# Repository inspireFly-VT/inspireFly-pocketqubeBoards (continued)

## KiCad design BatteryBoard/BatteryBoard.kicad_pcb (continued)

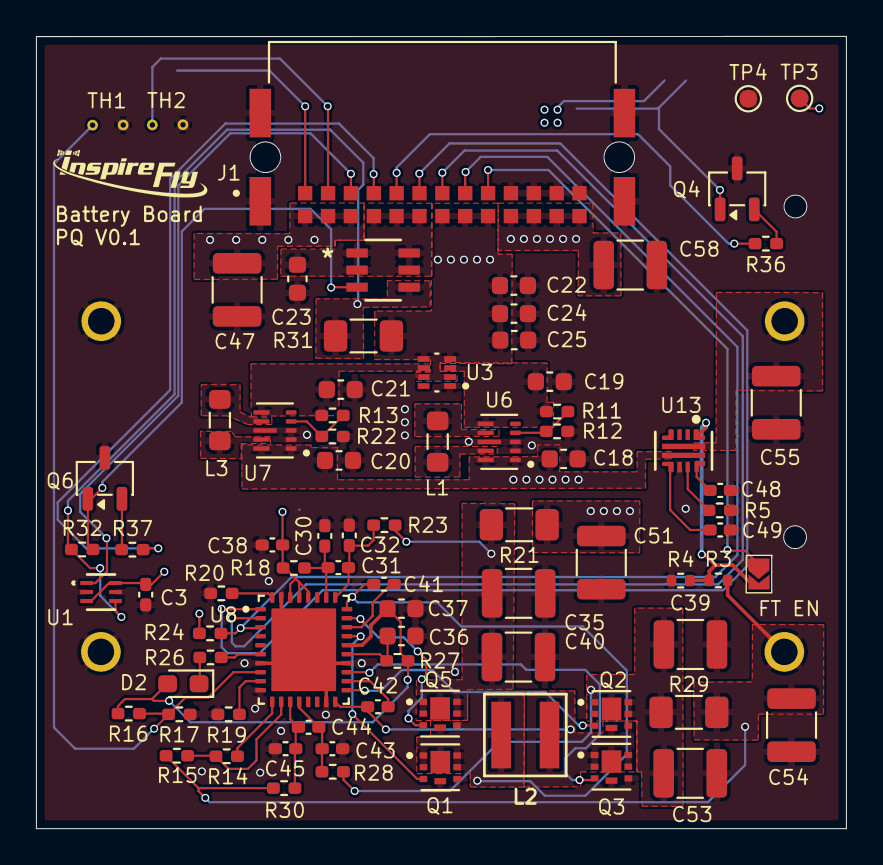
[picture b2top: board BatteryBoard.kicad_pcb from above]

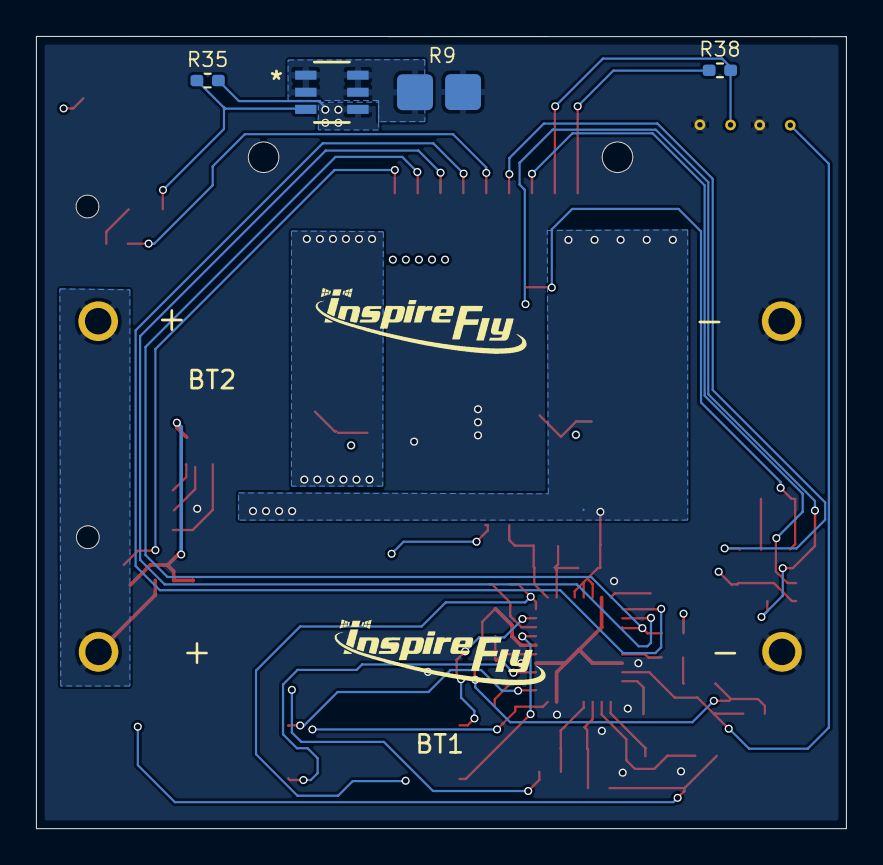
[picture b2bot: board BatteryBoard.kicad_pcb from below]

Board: 4 copper layers, 45.0 x 44.0 mm, 86 parts (6 on the bottom side), 56 nets.

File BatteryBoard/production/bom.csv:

Designator,Footprint,Quantity,Value,LCSC Part #
"BT1, BT2",BAT_BH123A,2,BH123A,
"C18, C19, C20, C21, C22, C23, C24, C25",0603,8,10uF,
"C3, C30, C32, C41, C42, C43, C45",0402,7,100nF,
"C31, C44",0402,2,470nF,
"C35, C39, C40, C47, C51, C53, C54, C55, C58",1210,9,22uF,
"C36, C37",0603,2,4.7uF,
C38,0402,1,1uF,
"C48, C49",0402,2,10nF,
D2,0603,1,LTST-S270KRKT,
J1,HARWIN_M55-7102642R,1,M55-7102642R,
JP1,SmallJumper,1,FTSW EN,
"L1, L3",0805,2,470nH,
L2,IND_SRP4020FA-2R2M_BRN,1,2.2uH,
"Q1, Q2, Q3, Q5",TRANS_PMPB11EN_115,4,"PMPB13XNE,115",
"Q4, Q6",SOT-23-3,2,"T2N7002AK,LM",
"R11, R13",0402,2,280k,
"R12, R19, R22",0402,3,50k,
R14,0402,1,82.5k,
R15,0402,1,143k,
R16,0402,1,6.2k,
R17,0402,1,36k,
"R18, R23, R27, R28, R30",0402,5,10,
R20,0402,1,40k,
"R21, R29, R31",1206,3,5m,
"R24, R26, R32, R35, R38",0402,5,10k,
R3,0402,1,649k,
"R36, R37",0402,2,100,
R4,0402,1,348k,
R5,0402,1,750,
R9,HeaterConnection,1,Heater,
"TH1, TH2",NRBG104F3435B2F,2,NRBG104F3435B2F,
TP3,TestPoint_Pad_D1.0mm,1,3.3V,
TP4,TestPoint_Pad_D1.0mm,1,GND,
U1,SOT_INA185_TEX,1,INA185A4IDRLR,
"U10, U2",SOT_V-T1-GE3_VIS-M,2,SI3477DV-T1-GE3,
U13,RPW0010A-MFG,1,TPS259472ARPWR,
U3,SOTFL50P160X60-8N,1,TPS2117DRLR,
"U6, U7",VREG_TPS63802DLAR,2,TPS63802DLAR,
U8,IC_BQ25756ERRVR,1,BQ25756ERRVR,

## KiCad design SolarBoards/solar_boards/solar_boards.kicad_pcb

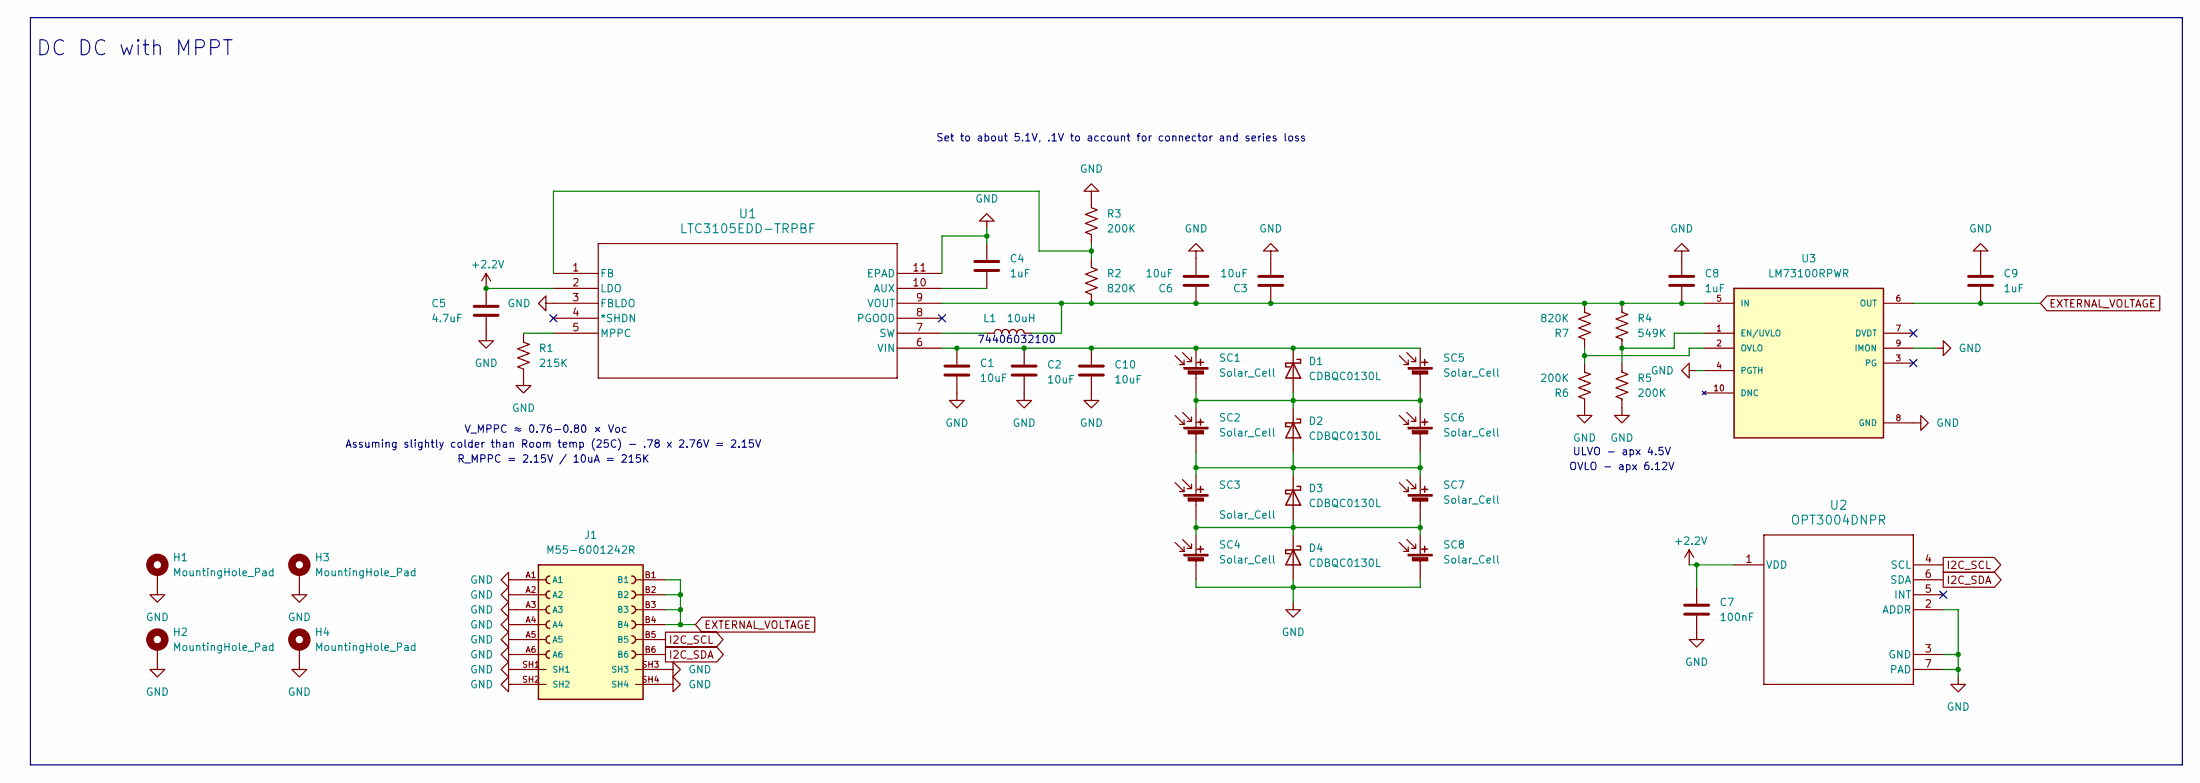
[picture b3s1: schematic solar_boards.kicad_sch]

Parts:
C1, C2, C3, C6, C10: 10uF; C_0603_1608Metric
C4, C8, C9: 1uF; C_0402_1005Metric_Pad0.74x0.62mm_HandSolder
C5: 4.7uF; C_0402_1005Metric_Pad0.74x0.62mm_HandSolder
C7: 100nF; C_0402_1005Metric_Pad0.74x0.62mm_HandSolder
D1, D2, D3, D4: CDBQC0130L; DIODFN100X60X55-2N
H1, H2, H3, H4: MountingHole_Pad; MountingHole_2mm_custom
J1: M55-6001242R; HARWIN_M55-6001242R; PARTREV 8; DigiKey_Part_Number 952-3835-1-ND
L1: 10uH; WE-LQFS_3818
R1: 215K; R_0402_1005Metric_Pad0.72x0.64mm_HandSolder
R2, R7: 820K; R_0402_1005Metric_Pad0.72x0.64mm_HandSolder
R3, R5, R6: 200K; R_0402_1005Metric_Pad0.72x0.64mm_HandSolder
R4: 549K; R_0402_1005Metric_Pad0.72x0.64mm_HandSolder
SC1, SC2, SC3, SC4, SC5, SC6, SC7, SC8: Solar_Cell; SOLAR_KXOB25-14X1F-TR
U1: LTC3105EDD-TRPBF; DFN-10_DD_LIT
U2: OPT3004DNPR; DNP0006A
U3: LM73100RPWR; IC_LM73100RPWR; PARTREV 08/2019

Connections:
+2.2V: C5.1, C7.1, U1.2 (LDO), U2.1 (VDD)
EXTERNAL_VOLTAGE: C9.1, J1.B1, J1.B2, J1.B3, J1.B4, U3.6 (OUT)
GND: C1.2, C2.2, C3.2, C4.1, C5.2, C6.2, C7.2, C8.2, C9.2, C10.2, D4.2 (A), H1.1 (1_1), H2.1 (1_1), H3.1 (1_1), H4.1 (1_1), J1.A1, J1.A2, J1.A3, J1.A4, J1.A5, J1.A6, J1.SH1, J1.SH2, J1.SH3, J1.SH4, R1.2, R3.1, R5.2, R6.1, SC4.2 (-), SC8.2 (-), U1.3 (FBLDO), U1.11 (EPAD), U2.2 (ADDR), U2.3 (GND), U2.7 (PAD), U3.4 (PGTH), U3.8 (GND), U3.9 (IMON)
I2C_SCL: J1.B5, U2.4 (SCL)
I2C_SDA: J1.B6, U2.6 (SDA)
unnamed: D1.2 (A), D2.1 (K), SC1.2 (-), SC2.1 (+), SC5.2 (-), SC6.1 (+)
unnamed: C1.1, C2.1, C10.1, D1.1 (K), SC1.1 (+), SC5.1 (+), U1.6 (VIN)
unnamed: D2.2 (A), D3.1 (K), SC2.2 (-), SC3.1 (+), SC6.2 (-), SC7.1 (+)
unnamed: D3.2 (A), D4.1 (K), SC3.2 (-), SC4.1 (+), SC7.2 (-), SC8.1 (+)
unnamed: C4.2, U1.10 (AUX)
unnamed: R2.1, R3.2, U1.1 (FB)
unnamed: R1.1, U1.5 (MPPC)
unnamed: L1.1, U1.7 (SW)
unnamed: C3.1, C6.1, C8.1, L1.2, R2.2, R4.1, R7.2, U1.9 (VOUT), U3.5 (IN)
unnamed: R4.2, R5.1, U3.1 (EN/UVLO)
unnamed: R6.2, R7.1, U3.2 (OVLO)

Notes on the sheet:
R_MPPC = 2.15V / 10uA = 215K
Assuming slightly colder than Room temp (25C) - .78 x 2.76V = 2.15V
ULVO - apx 4.5V
OVLO - apx 6.12V
74406032100
DC DC with MPPT
Set to about 5.1V, .1V to account for connector and series loss
V_MPPC ≈ 0.76-0.80 × Voc

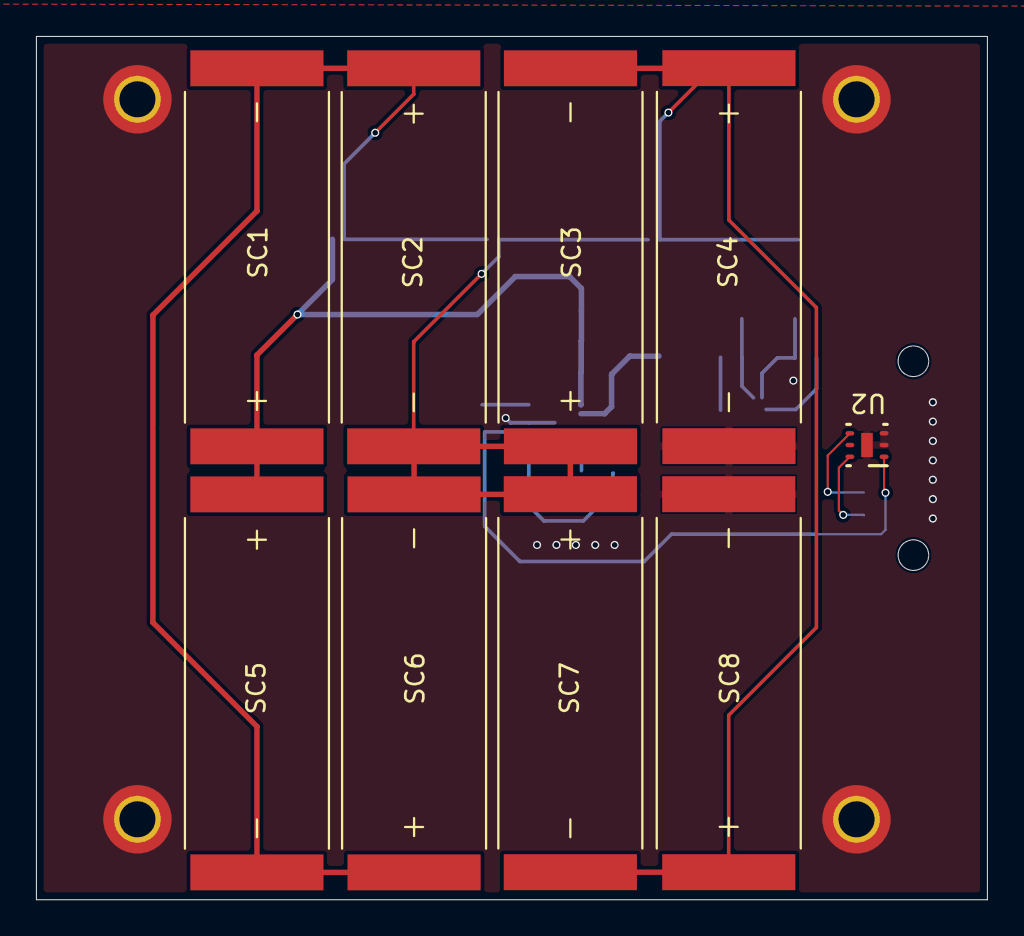
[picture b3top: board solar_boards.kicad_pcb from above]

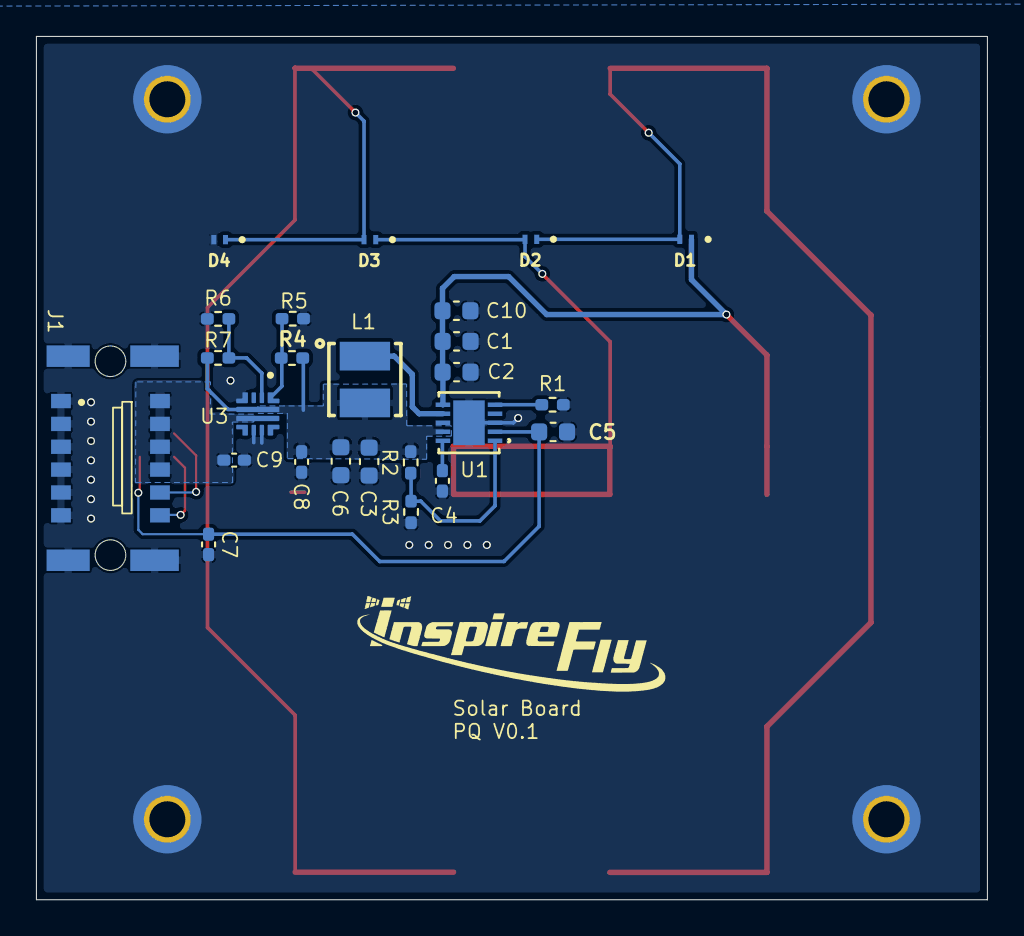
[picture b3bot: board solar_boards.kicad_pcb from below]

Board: 2 copper layers, 52.8 x 48.0 mm, 38 parts (25 on the bottom side), 16 nets.

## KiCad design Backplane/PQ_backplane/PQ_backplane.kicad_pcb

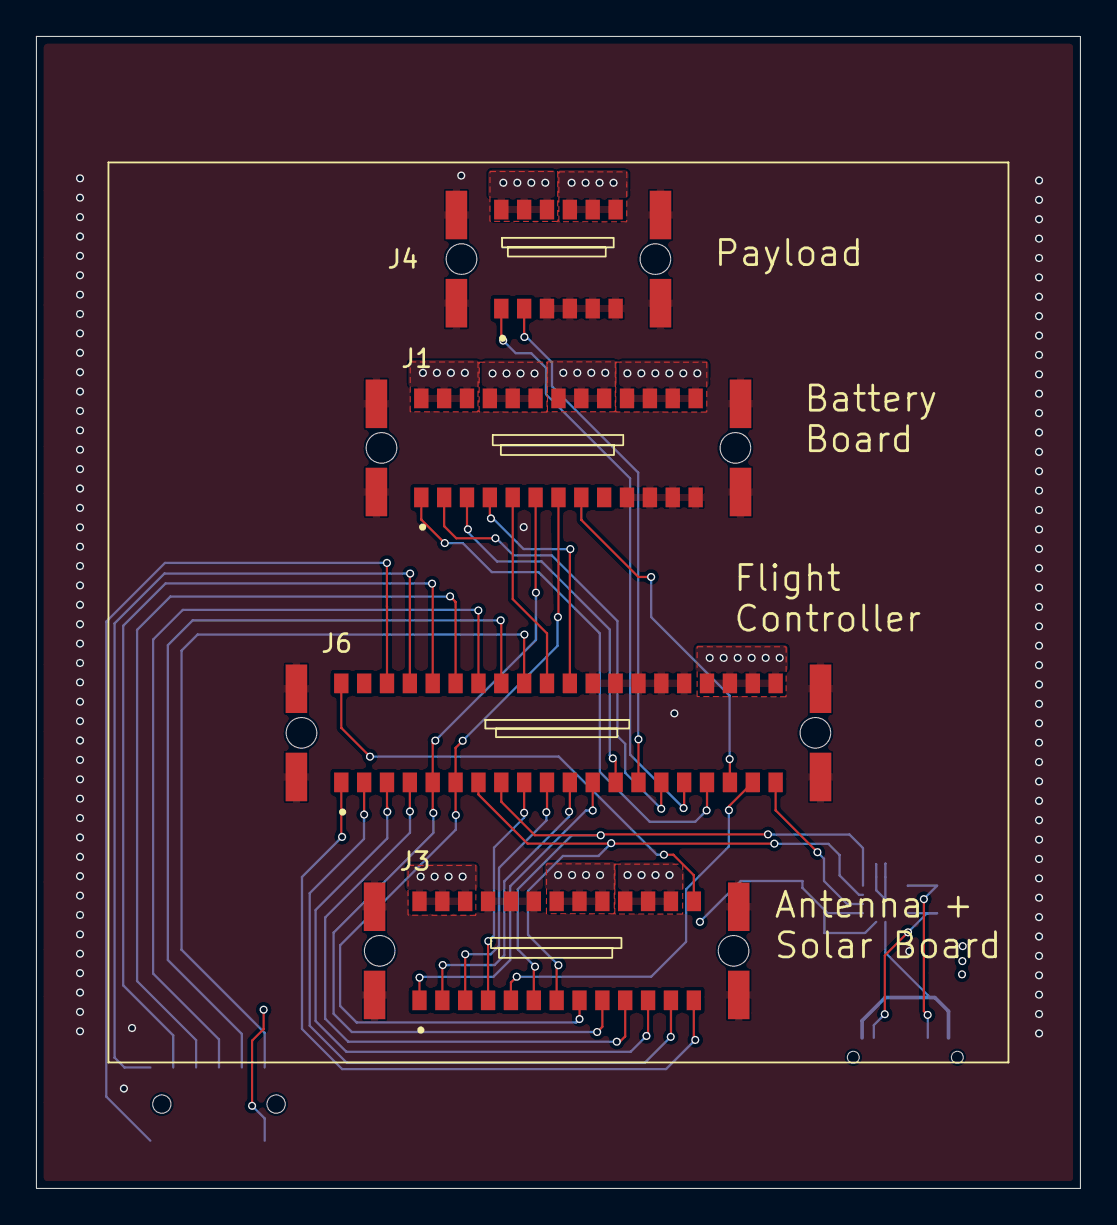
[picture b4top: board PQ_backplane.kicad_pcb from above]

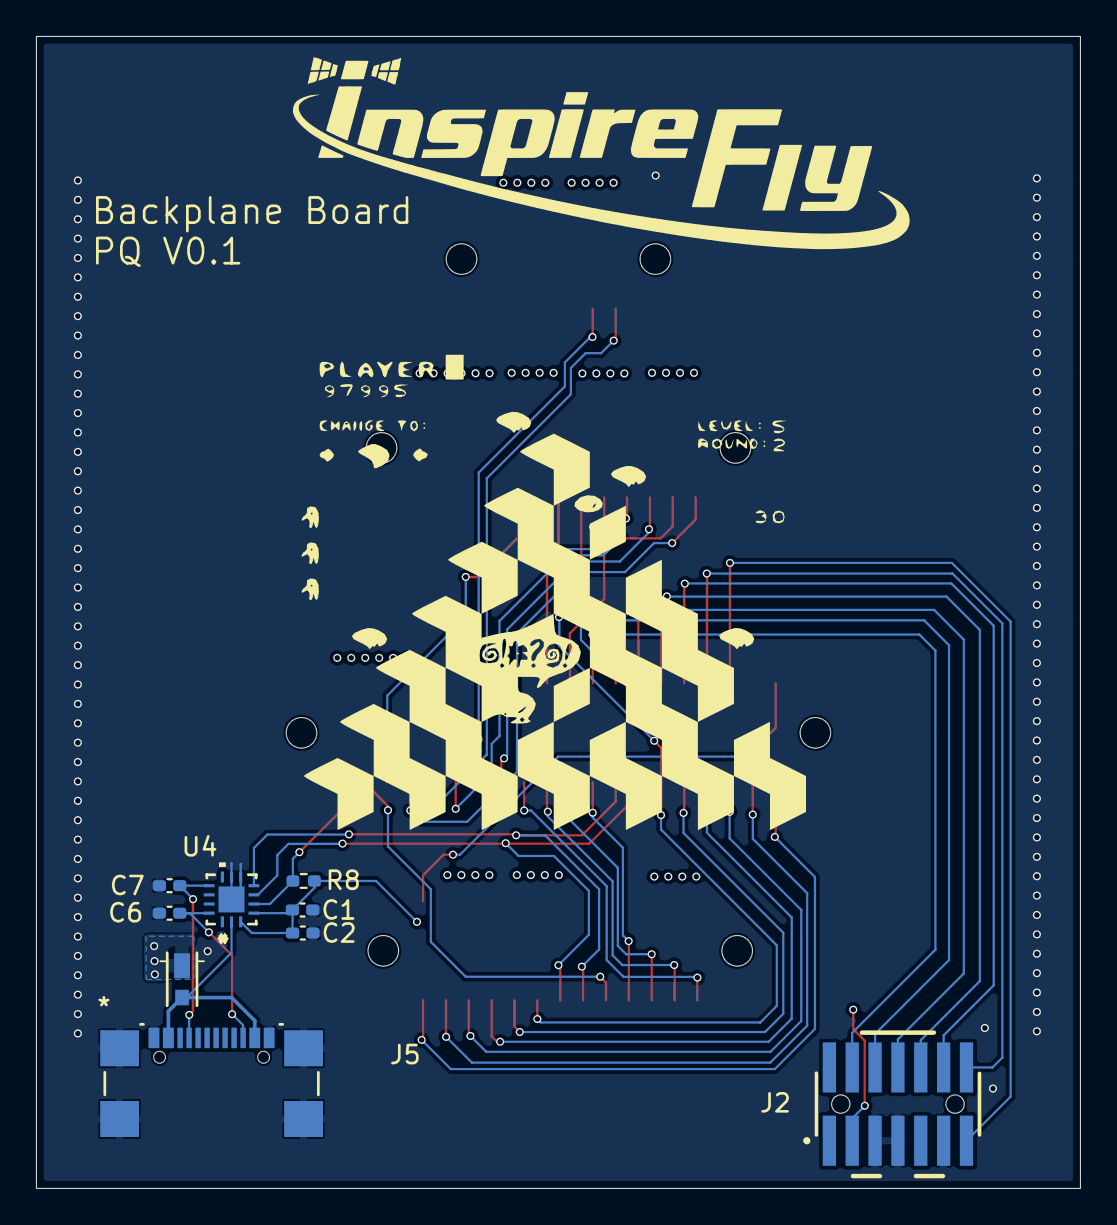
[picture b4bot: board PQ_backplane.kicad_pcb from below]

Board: 4 copper layers, 58.0 x 64.0 mm, 13 parts (9 on the bottom side), 38 nets.

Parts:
C1: 1uF; C_0402_1005Metric_Pad0.74x0.62mm_HandSolder
C2: 100nF; C_0402_1005Metric_Pad0.74x0.62mm_HandSolder
C6, C7: 470pF; C_0402_1005Metric_Pad0.74x0.62mm_HandSolder
D1: MSS2P2-M3/89A; DIODE_MSP3V3
J1, J3: M55-6002642R; HARWIN_M55-6002642R
J2: FTSH-107-01-L-DV-K-A; SAMTEC_FTSH-107-01-L-DV-K-A
J4: M55-6001242R; HARWIN_M55-6001242R
J5: USB4110-GF-A; USB4110-GF-A_GCT
J6: M55-6004042R; HARWIN_M55-6004042R
R8: 2.2k; R_0402_1005Metric_Pad0.72x0.64mm_HandSolder
U4: FUSB302BMPX; MLP14_2P5X2P5_ONS

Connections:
+3.3V: C1.1, C2.1, J1.B7, J1.B8, J1.B9, J2.03, J3.B1, J3.B2, J3.B3, J6.B17, J6.B18, J6.B19, J6.B20, R8.2, U4.3 (VDD), U4.4 (VDD)
ADC1_A1: J1.A3, J6.A13
ADC1_A2: J1.A2, J6.A15
ANT_SPI2_MISO: J3.A2, J6.A11
ANT_SPI2_MOSI: J3.A1, J6.A12
ANT_SPI2_NSS: J3.A3, J6.A10
ANT_SPI2_SCK: J3.A4, J6.A9
BATMANG_INT_DIN: J1.A8, J6.A18
BAT_HEAT_EN: J1.A5, J6.B10
BURN_WIRE_EN: J3.A5, J6.A19
CAN_H: J4.A1, J6.A16
CAN_L: J4.A2, J6.A14
DEBUG_LPUART_RX: J2.14, J6.B4
DEBUG_LPUART_TX: J2.13, J6.B3
EN_THERMISTOR_READ: J1.A1, J6.A17
EXTERNAL_VOLTAGE: D1.1 (K), J1.B1, J1.B2, J1.B3, J3.B10, J3.B11, J3.B12, J4.B4, J4.B5, J4.B6
GND: C1.2, C2.2, C6.2, C7.2, J1.A10, J1.A11, J1.A12, J1.A13, J1.SH1 (Shield), J1.SH2 (Shield), J1.SH3 (Shield), J1.SH4 (Shield), J2.05, J2.07, J2.11, J3.B4, J3.B5, J3.B6, J3.SH1 (Shield), J3.SH2 (Shield), J3.SH3 (Shield), J3.SH4 (Shield), J4.A3, J4.A4, J4.A5, J4.A6, J4.SH1 (Shield), J4.SH2 (Shield), J4.SH3 (Shield), J4.SH4 (Shield), J5.15 (Shield), J5.16 (Shield), J5.17 (Shield), J5.18 (Shield), J5.A1-B12 (GND), J5.A12-B1 (GND), J6.B12, J6.B13, J6.B14, J6.B15, J6.B16, J6.SH1 (Shield), J6.SH2 (Shield), J6.SH3 (Shield), J6.SH4 (Shield), U4.8 (GND), U4.9 (GND), U4.15 (EPAD)
I2C1_SCL: J3.A7, J6.A7, U4.6 (SCL)
I2C1_SDA: J3.A6, J6.A8, U4.7 (SDA)
I2C2_SCL: J1.A6, J3.A9, J6.A5
I2C2_SDA: J1.A7, J3.A8, J6.A6
I2C3_SCL: J3.A11, J6.A3
I2C3_SDA: J3.A10, J6.A4
I2C4_SCL: J3.A13, J6.A1
I2C4_SDA: J3.A12, J6.A2
JTCK/SWCLK: J2.06, J6.B8
JTDI: J2.10, J6.B6
JTMS/SWDIO: J2.04, J6.B9
NRST: J2.12, J6.B5
unnamed: D1.2 (A), J5.A4-B9 (VBUS), J5.A9-B4 (VBUS), U4.2 (VBUS)
unnamed: C7.1, J5.A5 (CC1), U4.11 (CC1)
unnamed: C6.1, J5.B5 (CC2), U4.14 (CC2)
PAYLOAD_3.3V: J1.B4, J1.B5, J1.B6, J4.B1, J4.B2, J4.B3
PAYLOAD_3.3V_EN: J1.A4, J6.B11
PROTECTED_VOLTAGE: J1.B10, J1.B11, J1.B12, J1.B13, J3.B7, J3.B8, J3.B9
RFM_RESET: J3.B13, J6.B1
SWO: J2.08, J6.B7
USBC_PD_INT_N: J6.A20, R8.1, U4.5 (INT_N)

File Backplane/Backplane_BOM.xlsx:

Distributor | Part Number | Part Description | Quantity Per Board
Digikey | CL05B104KA5NNNC | CAP CER 0.1UF 25V X7R 0402 | 1
Digikey | GRM155Z71A105KE01D | CAP CER 1UF 10V X7R 0402 | 1
Digikey | 885012005017 | CAP CER 470PF 10V C0G/NP0 0402 | 2
Digikey | ERA-2VEB2201X | RES 2.2K OHM 0.1% 1/10W 0402 | 1
Digikey | MSS2P2-M3/89A | DIODE SCHOTTKY 20V 2A DO219AD | 1
Digikey | FUSB302BMPX | IC USB TYPE C CTLR PROGR 14-MLP | 1
Digikey | M55-6002642R | CONN RCPT 26POS 0.05 GOLD SMD | 2
Digikey | FTSH-107-01-F-DV-K-P-TR | CONN HEADER SMD 14POS 1.27MM | 1
Digikey | M55-6001242R | CONN RCPT 12POS 0.05 GOLD SMD | 1
Digikey | USB4110-GF-A | CONN RCP USB2.0 TYP C 24P SMD RA | 1
Digikey | M55-6004042R | CONN RCPT 40POS 0.05 GOLD SMD | 1

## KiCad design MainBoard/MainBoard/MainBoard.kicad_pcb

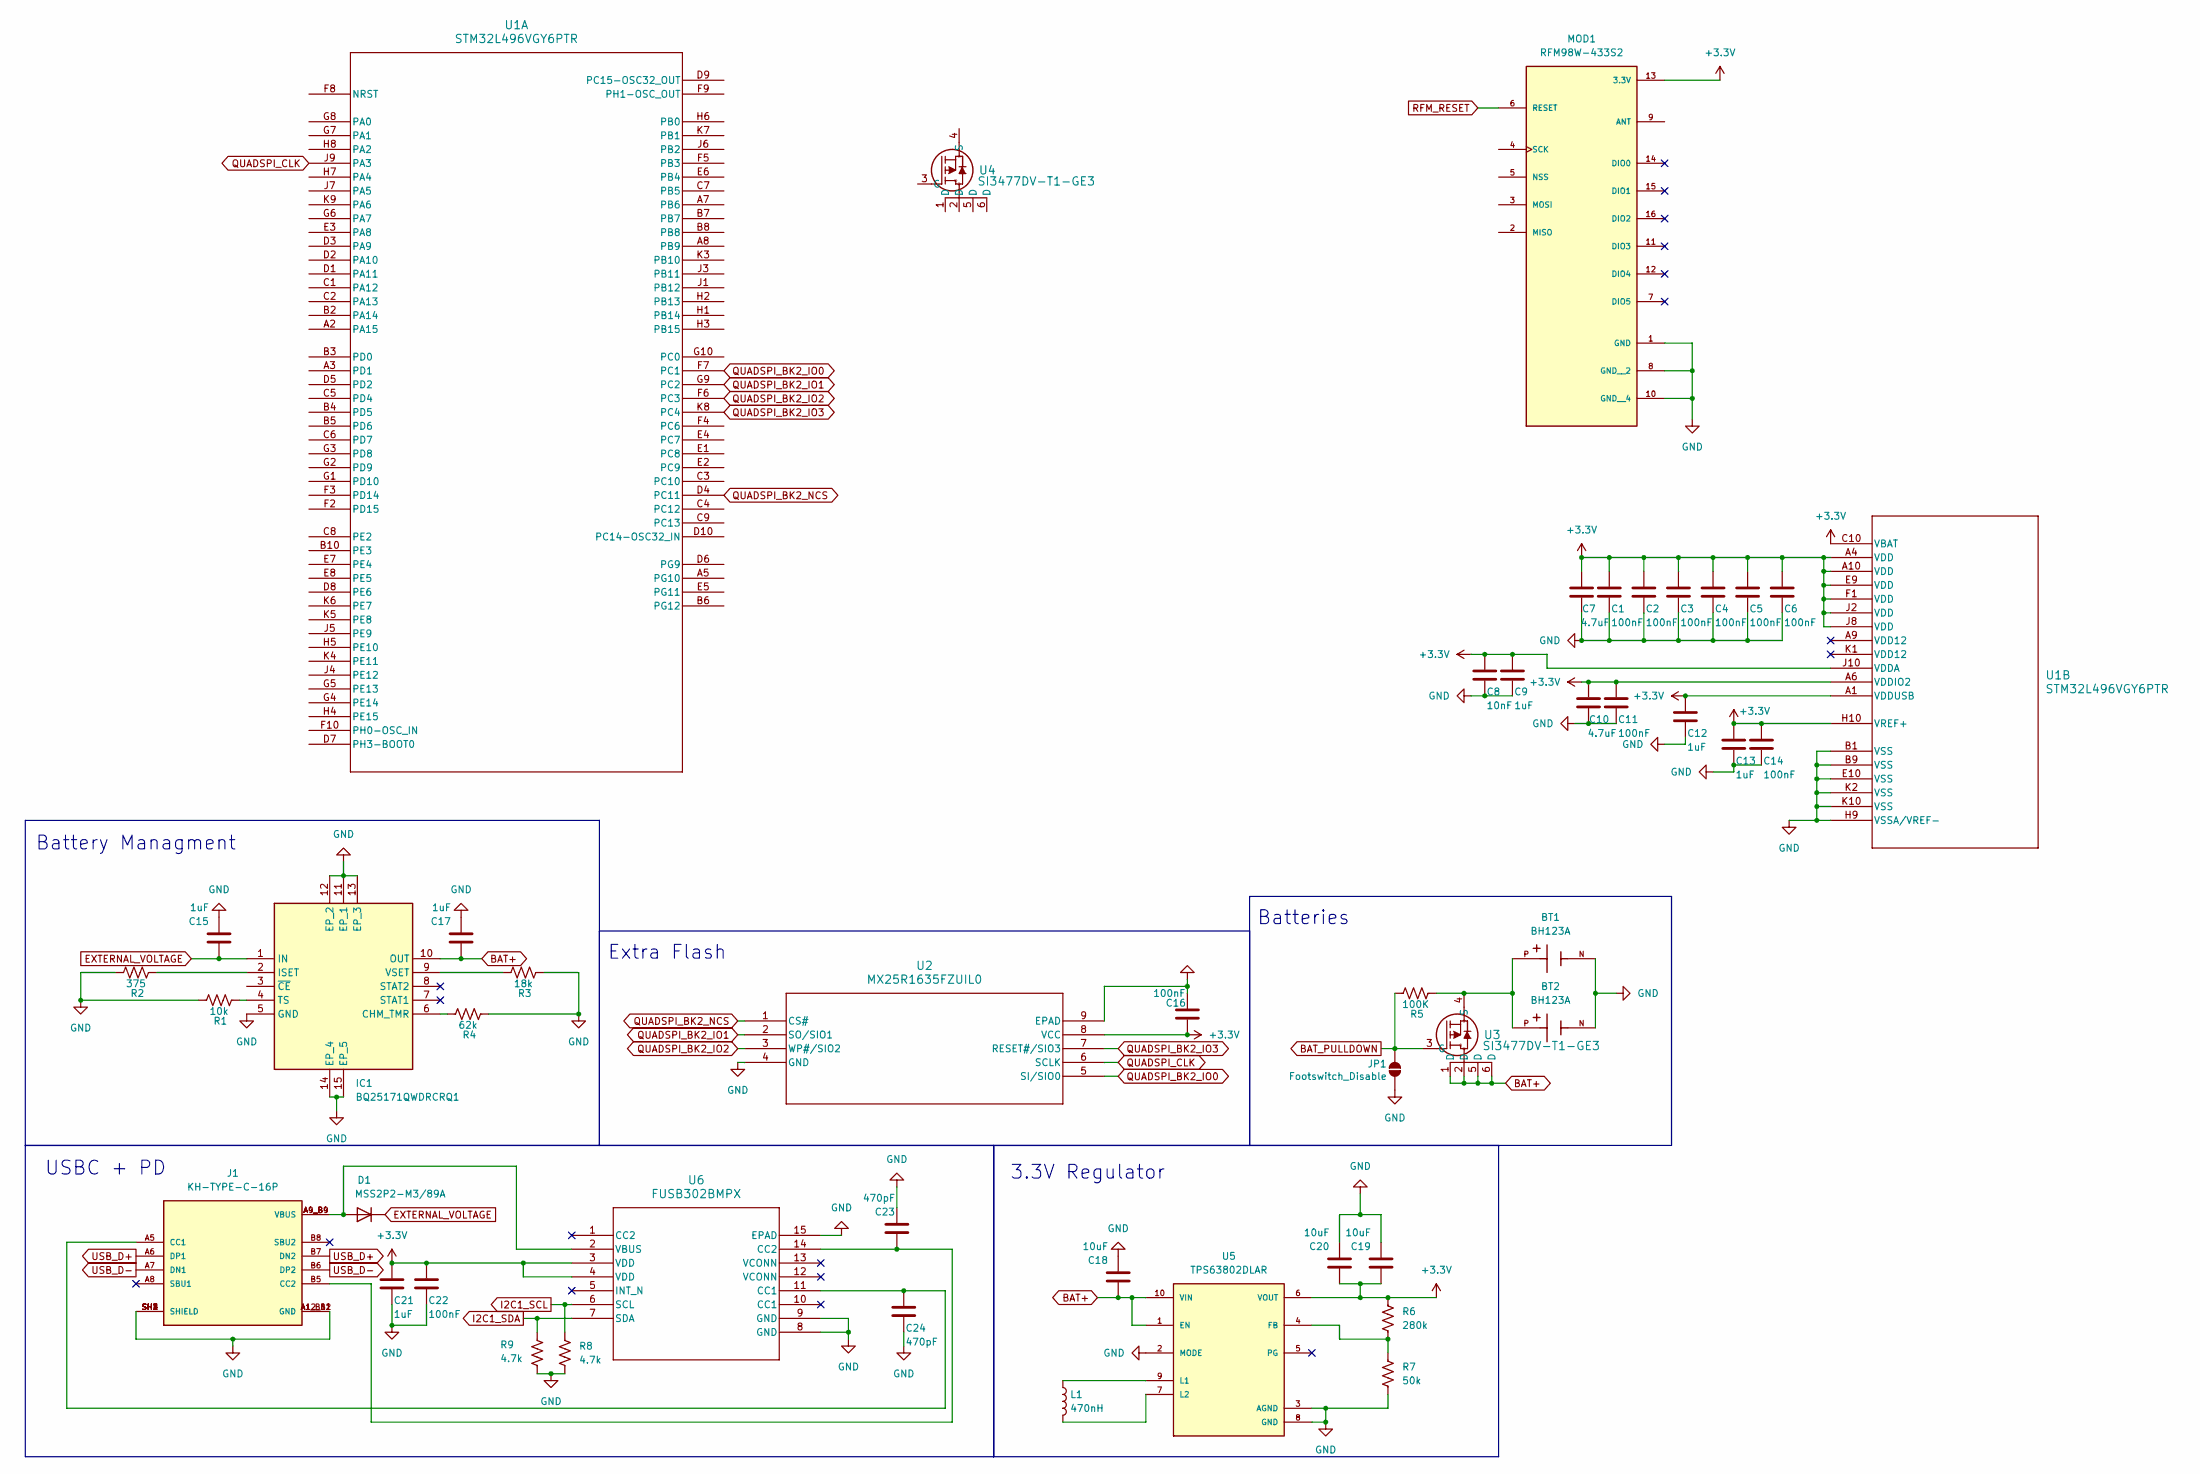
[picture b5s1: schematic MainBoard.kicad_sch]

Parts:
BT1, BT2: BH123A; BAT_BH123A; PARTREV E
C1, C2, C3, C4, C5, C6, C11, C14, C16, C22: 100nF; C_0402_1005Metric_Pad0.74x0.62mm_HandSolder
C7, C10: 4.7uF; C_0402_1005Metric_Pad0.74x0.62mm_HandSolder
C8: 10nF; C_0402_1005Metric_Pad0.74x0.62mm_HandSolder
C9, C12, C13, C15, C17, C21: 1uF; C_0402_1005Metric_Pad0.74x0.62mm_HandSolder
C18, C19, C20: 10uF; C_0402_1005Metric_Pad0.74x0.62mm_HandSolder
C23, C24: 470pF; C_0402_1005Metric_Pad0.74x0.62mm_HandSolder
D1: MSS2P2-M3/89A; DIODE_MSP3V3
IC1: BQ25171QWDRCRQ1; Mouser Part Number 595-BQ25171QWDRCRQ1
J1: KH-TYPE-C-16P; KINGHELM_KH-TYPE-C-16P; PARTREV A0
JP1: Footswitch_Disable; SolderJumper-2_P1.3mm_Open_TrianglePad1.0x1.5mm
L1: 470nH; L_0805_2012Metric_Pad1.15x1.40mm_HandSolder
MOD1: RFM98W-433S2; XCVR_RFM98W-433S2; PARTREV N/A
R1: 10k; R_0402_1005Metric_Pad0.72x0.64mm_HandSolder
R2: 375; R_0402_1005Metric_Pad0.72x0.64mm_HandSolder
R3: 18k; R_0402_1005Metric_Pad0.72x0.64mm_HandSolder
R4: 62k; R_0402_1005Metric_Pad0.72x0.64mm_HandSolder
R5: 100K; R_0402_1005Metric_Pad0.72x0.64mm_HandSolder
R6: 280k; R_0402_1005Metric_Pad0.72x0.64mm_HandSolder
R7: 50k; R_0402_1005Metric_Pad0.72x0.64mm_HandSolder
R8, R9: 4.7k; R_0402_1005Metric_Pad0.72x0.64mm_HandSolder
U1: STM32L496VGY6PTR; STM32L496VGY6TR
U2: MX25R1635FZUIL0; USON-8L-2X3X0P6_MAC
U3, U4: SI3477DV-T1-GE3; SOT_V-T1-GE3_VIS-M
U5: TPS63802DLAR; VREG_TPS63802DLAR; PARTREV B
U6: FUSB302BMPX; MLP14_2P5X2P5_ONS

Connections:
+3.3V: C1.1, C2.1, C3.1, C4.1, C5.1, C6.1, C7.1, C8.1, C9.1, C10.1, C11.1, C12.1, C13.1, C14.1, C16.2, C19.1, C20.1, C21.1, C22.1, MOD1.13 (3.3V), R6.1, U1.A1 (VDDUSB), U1.A4 (VDD), U1.A6 (VDDIO2), U1.A10 (VDD), U1.C10 (VBAT), U1.E9 (VDD), U1.F1 (VDD), U1.H10 (VREF+), U1.J2 (VDD), U1.J8 (VDD), U1.J10 (VDDA), U2.8 (VCC), U5.6 (VOUT), U6.3 (VDD), U6.4 (VDD); also elsewhere on the board
BAT+: C17.1, C18.1, IC1.10 (OUT), U3.1 (D), U3.2 (D), U3.5 (D), U3.6 (D), U5.1 (EN), U5.10 (VIN)
BAT_PULLDOWN: JP1.2 (B), R5.1, U3.3 (G)
EXTERNAL_VOLTAGE: C15.1, D1.1 (K), IC1.1 (IN)
GND: BT1.N, BT2.N, C1.2, C2.2, C3.2, C4.2, C5.2, C6.2, C7.2, C8.2, C9.2, C10.2, C11.2, C12.2, C13.2, C14.2, C15.2, C16.1, C17.2, C18.2, C19.2, C20.2, C21.2, C22.2, C23.2, C24.2, IC1.5 (GND), IC1.11 (EP_1), IC1.12 (EP_2), IC1.13 (EP_3), IC1.14 (EP_4), IC1.15 (EP_5), J1.A1_B12 (GND), J1.A12_B1 (GND), J1.SH1 (SHIELD), J1.SH2 (SHIELD), J1.SH3 (SHIELD), J1.SH4 (SHIELD), JP1.1 (A), MOD1.1 (GND), MOD1.8 (GND__2), MOD1.10 (GND__4), R1.1, R2.1, R3.2, R4.2, R7.2, R8.2, R9.1, U1.B1 (VSS), U1.B9 (VSS), U1.E10 (VSS), U1.H9 (VSSA/VREF-), U1.K2 (VSS), U1.K10 (VSS), U2.4 (GND), U2.9 (EPAD), U5.2 (MODE), U5.3 (AGND), U5.8 (GND), U6.8 (GND), U6.9 (GND), U6.15 (EPAD); also elsewhere on the board
I2C1_SCL: R8.1, U6.6 (SCL)
I2C1_SDA: R9.2, U6.7 (SDA)
unnamed: D1.2 (A), J1.A4_B9 (VBUS), J1.A9_B4 (VBUS), U6.2 (VBUS)
unnamed: IC1.6 (CHM_TMR), R4.1
unnamed: IC1.2 (ISET), R2.2
unnamed: IC1.4 (TS), R1.2
unnamed: IC1.9 (VSET), R3.1
unnamed: C24.1, J1.A5 (CC1), U6.11 (CC1)
unnamed: C23.1, J1.B5 (CC2), U6.14 (CC2)
unnamed: BT1.P, BT2.P, R5.2, U3.4 (S)
unnamed: R6.2, R7.1, U5.4 (FB)
unnamed: L1.1, U5.9 (L1)
unnamed: L1.2, U5.7 (L2)
QUADSPI_BK2_IO0: U1.F7 (PC1), U2.5 (SI/SIO0)
QUADSPI_BK2_IO1: U1.G9 (PC2), U2.2 (SO/SIO1)
QUADSPI_BK2_IO2: U1.F6 (PC3), U2.3 (WP#/SIO2)
QUADSPI_BK2_IO3: U1.K8 (PC4), U2.7 (RESET#/SIO3)
QUADSPI_BK2_NCS: U1.D4 (PC11), U2.1 (CS#)
QUADSPI_CLK: U1.J9 (PA3), U2.6 (SCLK)
RFM_RESET: MOD1.6 (RESET)
USB_D+: J1.A6 (DP1), J1.B7 (DN2)
USB_D-: J1.A7 (DN1), J1.B6 (DP2)

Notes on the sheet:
Extra Flash
Batteries
Battery Managment
3.3V Regulator
USBC + PD

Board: 6 copper layers, 48 parts (2 on the bottom side), 26 nets, no tracks yet.

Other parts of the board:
C21#2: 1uF; C_0402_1005Metric_Pad0.74x0.62mm_HandSolder

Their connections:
+3.3V: C21#2.1; also elsewhere on the board
GND: C21#2.2; also elsewhere on the board

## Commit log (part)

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2025-09-02 Added .step
2025-09-03 Schematic work
2025-09-21 Sorting Schematic
2025-09-28 Locking Files
    See LOCK.txt
2025-09-28 Pushing Lock File
2025-09-28 Updated Lock File
    List changes done to files:
    Ex. Changes to mainboard.kicad_pcb
    Changed value of R1 to 10K from 1K
    etc.
2025-09-28 LOCKING File
2025-09-28 Finished work on something
    Say what you did
2025-10-09 working on imu in schematic
2025-10-09 yoshita worked on IMU pins, about half done with connecting the pins
2025-10-09 ended the session on working on IMU
2025-10-12 pushing Lock
2025-10-12 Add CAN transceiver - removed radio module
2025-10-20 Integrated BQ25756E along with schematic changes
    Removed old Battery management, replaced with BQ25756E. Schematic work complete along with external part finding.
    Dedicated section to I2C pull ups.
    Moved around items in schematics for better look.
2025-10-20 Changed bulk cap values
    Removed parallel 22uF 0402 for bulks on battery management. Replaced with 47uF 1206 due to over voltage issues.
2025-11-02 Adding cutoff circuits and others
    Added 3.3V and Bat Voltage current sense and cutoff cirucits
    Also changed footprints to non-hand solder for 0402
    And changed I2C pullups to an array
2025-11-02 IMU Label Adding
    Added some labels from Yoshita
2025-11-07 imu changed from crystal to external mcu clock- yoshita
2025-11-10 Fixed values/issues on BQ chip
2025-11-11 Footprint edits and board setup
2025-11-12 Added a good amount of STM connections
2025-11-16 Pushing new project + files
2025-11-16 Removing Lock
2025-11-17 Pushing more schematic changes
    Added ST link connections
    Added Harwin M55
    Changed some items for Battery managment
2025-11-17 Did some placement
    Did most the caps for MCU, general placement for fill zones
2025-11-17 Waiting on board sizes to finish placement
    All parts placed, some light schematic and checking work still needs to be done
2025-11-18 Still waiting on final board size....
2025-11-18 Cap routing
    Capacitor Routing near STM, can be moved around if needed
2025-11-19 Happy with placement
    Got sizes from mechanical, adjusted placement accordingly
2025-11-20 Added some routing
    Routing done for f.cu BQ chip and some others
2025-11-20 Routed a bunch of stuff
    Most if not all fill zones are done
    Most if not all cap to 3.3V are done
    To start working on communication
2025-11-21 Changes to USB and routing
    Added ESD protection IC
    Routed USB Differential to STM
2025-12-01 Added E-Fuse/ battery protection IC
    Added and routed new IC for battery
    - will have to figure out cutoff but that can be done later imo
2025-12-01 Pushing BOM and changes
    Had to change one resistor footprint and routing
2025-12-19 Routing
2025-12-24 Routing updates
2025-12-25 More Routing
2026-01-05 Mounting pad additions, footswitch and BOM changes
2026-01-08 Final Board Order Changes for Mainboard
2026-01-15 To be reviewed v0.1 (#2)
    V0.1 Mainboard complete
2026-01-15 Pushing Discrepancy Log
2026-01-15 Updated Discrepancy Log
2026-02-02 Adjust traces to 4mil
2026-02-02 Adjust trace width to 4 mils
    There is a courtyards overlap error with J1 and BT2. I think it will still work out
2026-02-06 Battery Board implementation
    Need to add pin assignments
2026-02-07 Updated thermistor footprint and added pin connections
2026-02-16 Changes to solar boards
2026-02-22 started battery harvester
    imported harvester and started wiring up
2026-02-28 began wiring
2026-03-09 Pushing Backplane board files
2026-03-10 Pushing changes to backplane
2026-03-15 Pushing Mainboard Split Up
    Mainboard will be obsoleted soon
    Battery Board and Flight Controller created
    Battery Board - Good amount of routing done, additional area will be used for SuperCaps
2026-03-15 Modify Backplane for Battery Board
2026-03-15 Flight Controller updates
2026-03-16 Updates to FC
2026-03-28 some updates/ will find new solar cells
2026-03-29 Sorting files/ cleanup
2026-03-29 Updated outline
2026-04-01 Fixed outline
2026-04-11 added new boost converter and added elements
2026-04-11 Board sizes for FC and routing. slight Backplane changes
2026-04-27 boost converter values, will add solar cell
2026-05-01 Solar Board Schematic and Routing
2026-05-03 Routing and schematic work on most boards
2026-05-04 Finalize board work + BOM work
